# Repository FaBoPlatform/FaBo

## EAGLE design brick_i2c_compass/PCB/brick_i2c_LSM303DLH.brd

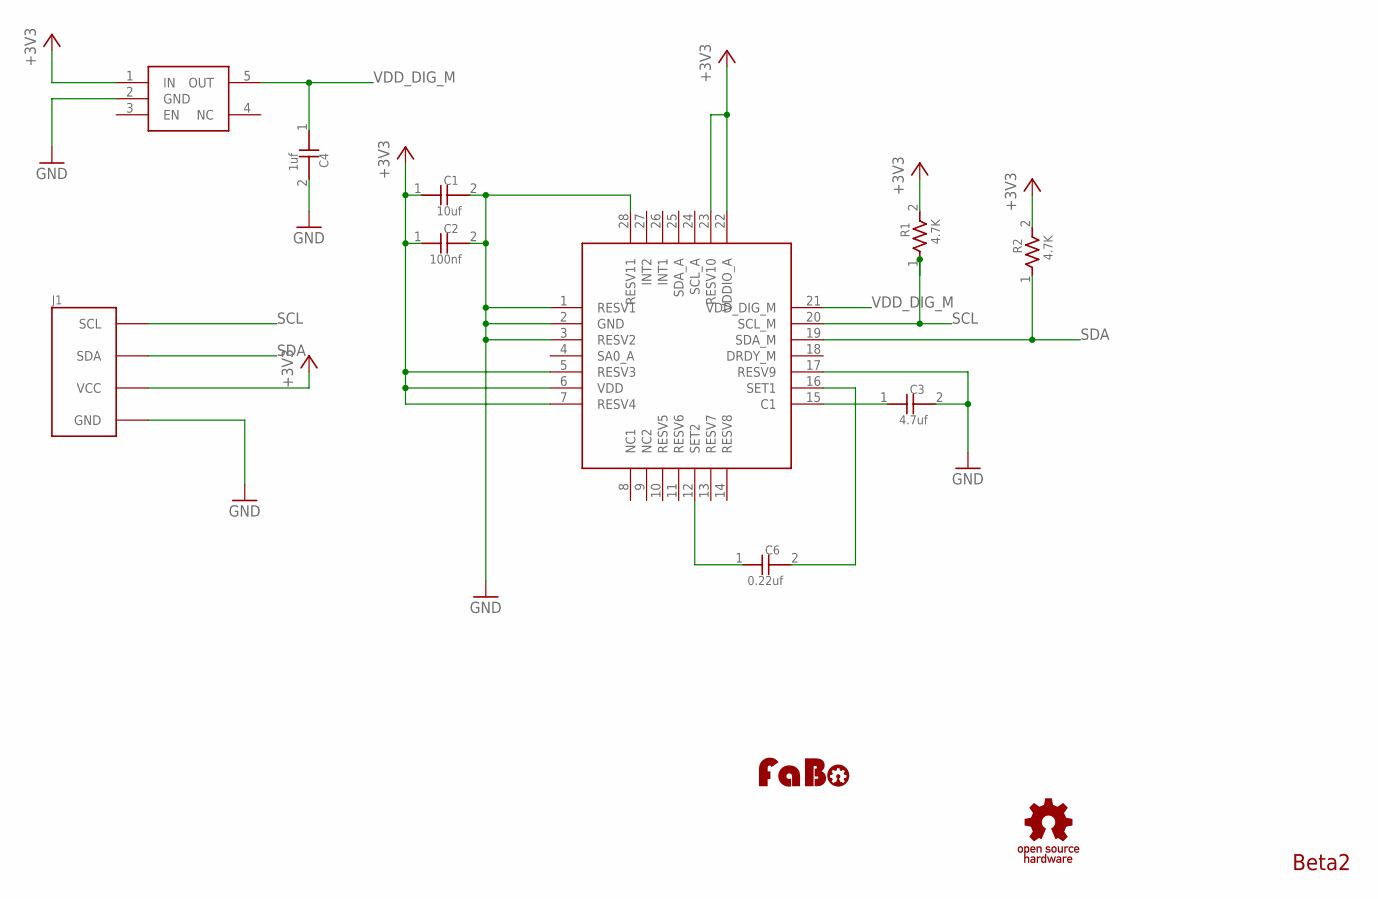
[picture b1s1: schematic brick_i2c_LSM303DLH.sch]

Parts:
C1: 10uf; 0603
C2: 100nf; 0603
C3: 4.7uf; 0603
C4: 1uf; 0603
C6: 0.22uf; 0603
J1: BRICK_I2C
R1, R2: 4.7K; 0603
U$2: ST-LSM303DLH; LGA-28
U$3: TI-TLV70018DDCT; SOT23-5
U$4: LOGO_OSHW_T-M; LOGO_OSHW_T_M
U$5: LOGO_FABO-M; LOGO_FABO_M

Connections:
+3V3: C1.1, C2.1, J1.VCC, R1.2, R2.2, U$2.5 (RESV3), U$2.6 (VDD), U$2.7 (RESV4), U$2.22 (VDDIO_A), U$2.23 (RESV10), U$3.1 (IN)
GND: C1.2, C2.2, C3.2, C4.2, J1.GND, U$2.1 (RESV1), U$2.2 (GND), U$2.3 (RESV2), U$2.17 (RESV9), U$2.28 (RESV11), U$3.2 (GND)
unnamed: C6.1, U$2.12 (SET2)
unnamed: C6.2, U$2.16 (SET1)
unnamed: C3.1, U$2.15 (C1)
SCL: J1.SCL, R1.1, U$2.20 (SCL_M)
SDA: J1.SDA, R2.1, U$2.19 (SDA_M)
VDD_DIG_M: C4.1, U$2.21 (VDD_DIG_M), U$3.5 (OUT)

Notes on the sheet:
Beta2

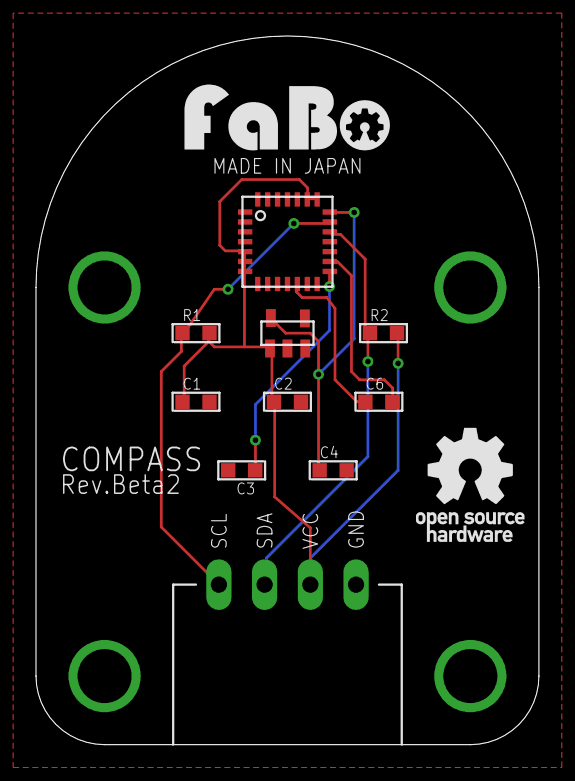
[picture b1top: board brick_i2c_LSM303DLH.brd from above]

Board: 2 copper layers, 27.9 x 39.4 mm, 12 parts (0 on the bottom side), 8 nets.

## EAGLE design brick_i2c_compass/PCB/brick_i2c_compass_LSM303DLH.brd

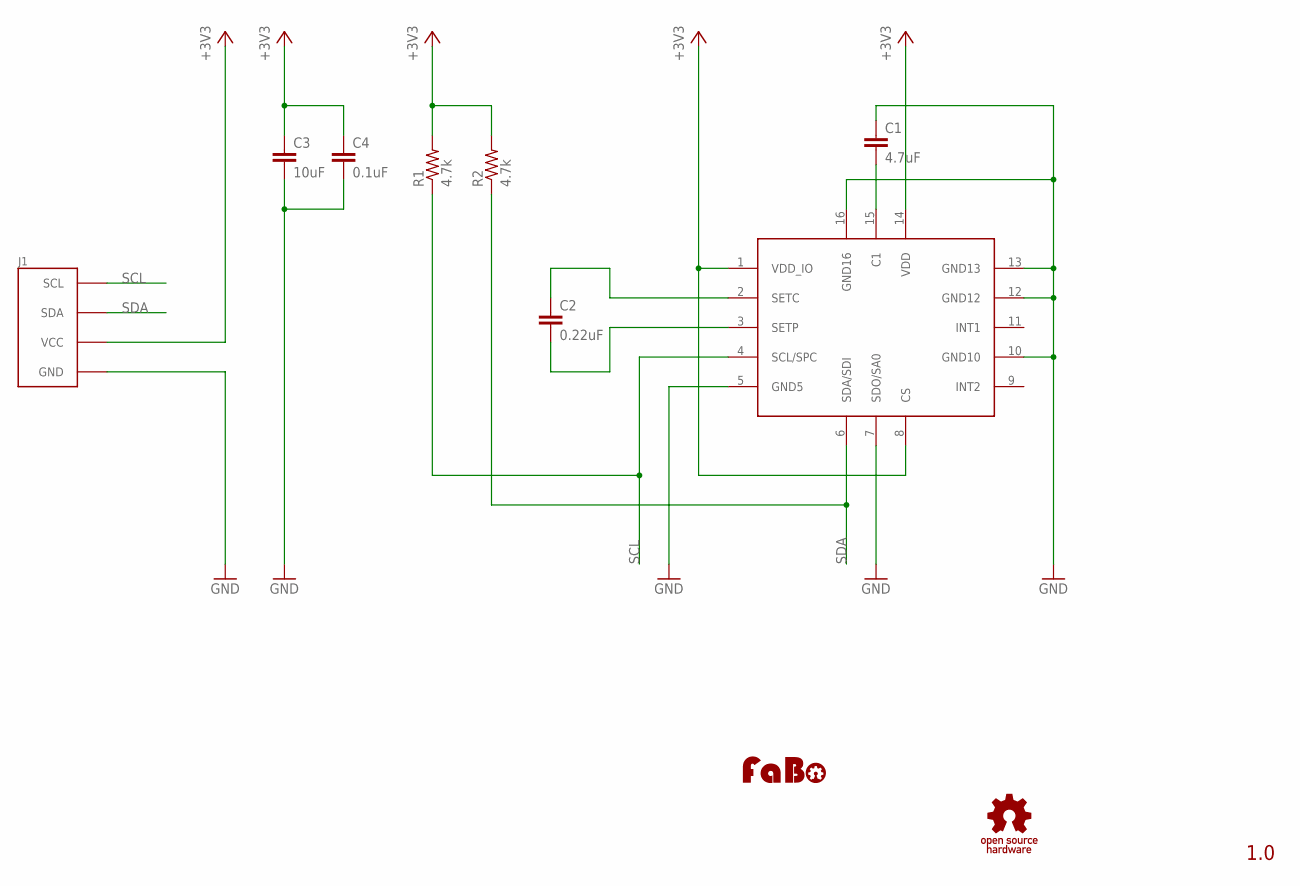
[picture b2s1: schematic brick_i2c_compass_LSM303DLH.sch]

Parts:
C1: 4.7uF; EIA0603
C2: 0.22uF; EIA0603
C3: 10uF; EIA0603
C4: 0.1uF; EIA0603
J1: BRICK_I2C
R1, R2: 4.7k; EIA0603
U$2: ST-LSM303DLH
U$4: LOGO_OSHW_T-M; LOGO_OSHW_T_M
U$5: LOGO_FABO-M; LOGO_FABO_M

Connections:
+3V3: C3.1, C4.1, J1.VCC, R1.2, R2.2, U$2.1 (VDD_IO), U$2.8 (CS), U$2.14 (VDD)
GND: C1.1, C3.2, C4.2, J1.GND, U$2.5 (GND5), U$2.7 (SDO/SA0), U$2.10 (GND10), U$2.12 (GND12), U$2.13 (GND13), U$2.16 (GND16)
unnamed: C2.1, U$2.2 (SETC)
unnamed: C2.2, U$2.3 (SETP)
unnamed: C1.2, U$2.15 (C1)
SCL: J1.SCL, R1.1, U$2.4 (SCL/SPC)
SDA: J1.SDA, R2.1, U$2.6 (SDA/SDI)

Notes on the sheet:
1.0

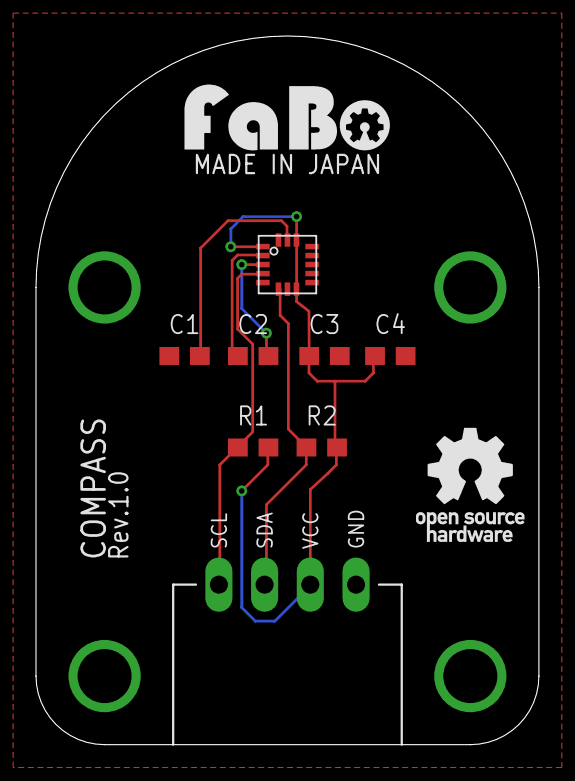
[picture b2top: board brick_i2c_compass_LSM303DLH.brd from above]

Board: 2 copper layers, 27.9 x 39.4 mm, 10 parts (0 on the bottom side), 7 nets.

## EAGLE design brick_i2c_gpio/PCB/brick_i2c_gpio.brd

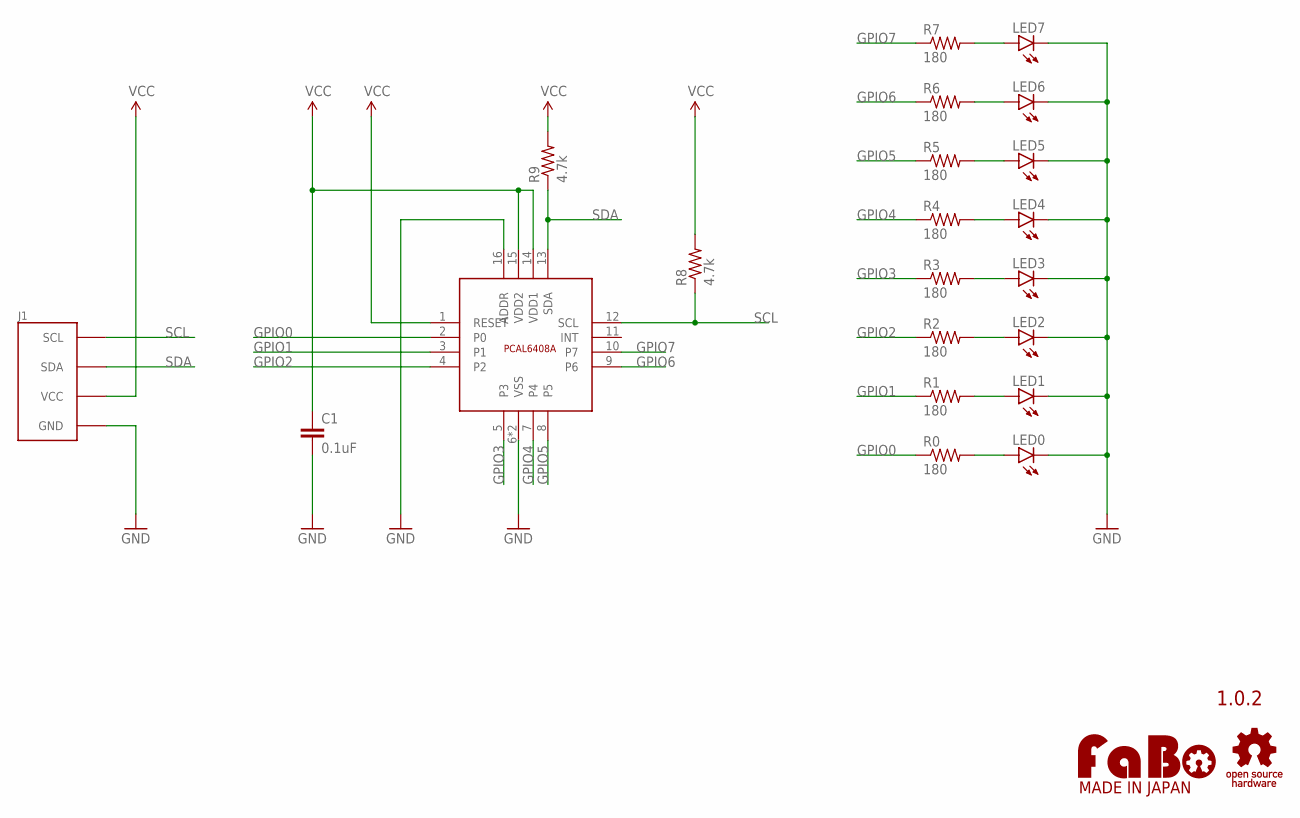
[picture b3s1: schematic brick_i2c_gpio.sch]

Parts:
C1: 0.1uF; EIA0603
J1: BRICK_I2C
LED0, LED1, LED2, LED3, LED4, LED5, LED6, LED7: LED-EIA0603; EIA0603-LED
R0, R1, R2, R3, R4, R5, R6, R7: 180; EIA0603
R8, R9: 4.7k; EIA0603
U$2: LOGO_OSHW-T_M; LOGO_OSHW_T_M
U$4: LOGO_FABO-M; LOGO_FABO_M
U$5: NX-PCAL6408A; NXP-PCAL6408A

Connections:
GND: C1.2, J1.GND, LED0.C, LED1.C, LED2.C, LED3.C, LED4.C, LED5.C, LED6.C, LED7.C, U$5.6 (VSS), U$5.16 (ADDR), U$5.17 (VSS)
GPIO0: R0.1, U$5.2 (P0)
GPIO1: R1.1, U$5.3 (P1)
GPIO2: R2.1, U$5.4 (P2)
GPIO3: R3.1, U$5.5 (P3)
GPIO4: R4.1, U$5.7 (P4)
GPIO5: R5.1, U$5.8 (P5)
GPIO6: R6.1, U$5.9 (P6)
GPIO7: R7.1, U$5.10 (P7)
unnamed: LED7.A, R7.2
unnamed: LED6.A, R6.2
unnamed: LED5.A, R5.2
unnamed: LED4.A, R4.2
unnamed: LED3.A, R3.2
unnamed: LED2.A, R2.2
unnamed: LED1.A, R1.2
unnamed: LED0.A, R0.2
SCL: J1.SCL, R8.1, U$5.12 (SCL)
SDA: J1.SDA, R9.1, U$5.13 (SDA)
VCC: C1.1, J1.VCC, R8.2, R9.2, U$5.1 (RESET), U$5.14 (VDD1), U$5.15 (VDD2)

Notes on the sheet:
1.0.2

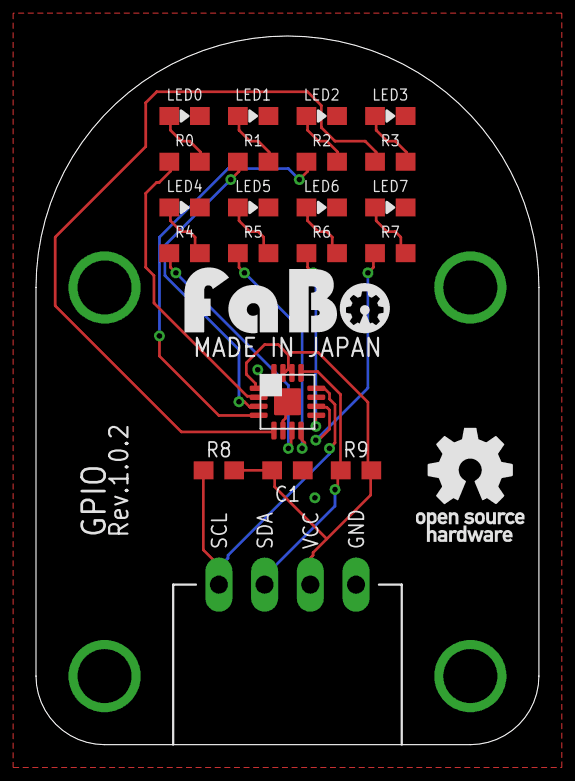
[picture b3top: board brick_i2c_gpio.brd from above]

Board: 2 copper layers, 27.9 x 39.4 mm, 23 parts (0 on the bottom side), 20 nets.

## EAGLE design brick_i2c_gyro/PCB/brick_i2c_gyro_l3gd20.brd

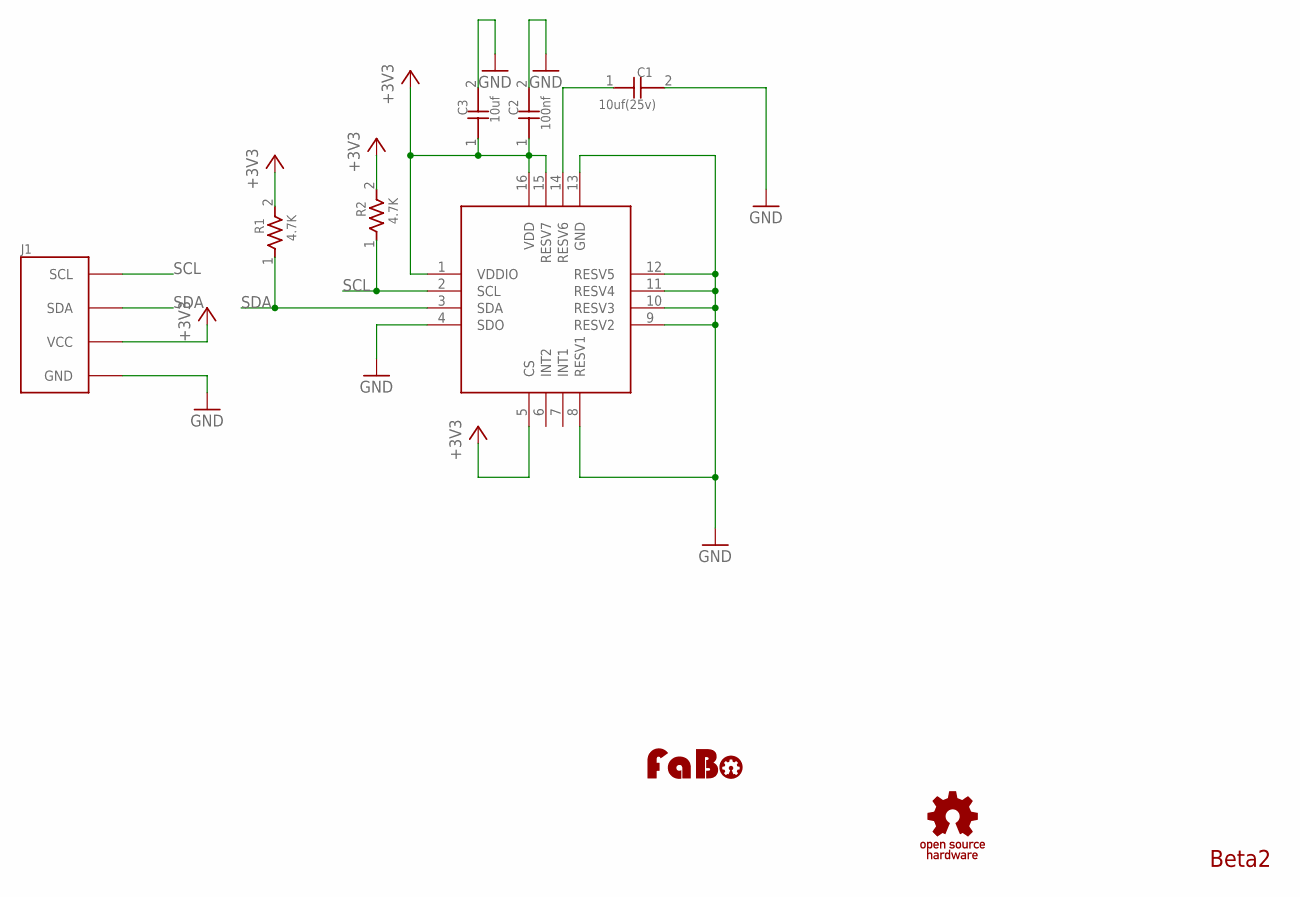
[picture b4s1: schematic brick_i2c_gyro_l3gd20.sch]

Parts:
C1: 10uf(25v); 0603
C2: 100nf; 0603
C3: 10uf; 0603
J1: BRICK_I2C
R1, R2: 4.7K; 0603
U$1: LOGO_OSHW_T-M; LOGO_OSHW_T_M
U$3: ST-L3GD20; LGA-16
U$4: LOGO_FABO-M; LOGO_FABO_M

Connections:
+3V3: C2.1, C3.1, J1.VCC, R1.2, R2.2, U$3.1 (VDDIO), U$3.5 (CS), U$3.15 (RESV7), U$3.16 (VDD)
GND: C1.2, C2.2, C3.2, J1.GND, U$3.4 (SDO), U$3.8 (RESV1), U$3.9 (RESV2), U$3.10 (RESV3), U$3.11 (RESV4), U$3.12 (RESV5), U$3.13 (GND)
unnamed: C1.1, U$3.14 (RESV6)
SCL: J1.SCL, R2.1, U$3.2 (SCL)
SDA: J1.SDA, R1.1, U$3.3 (SDA)

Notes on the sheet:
Beta2

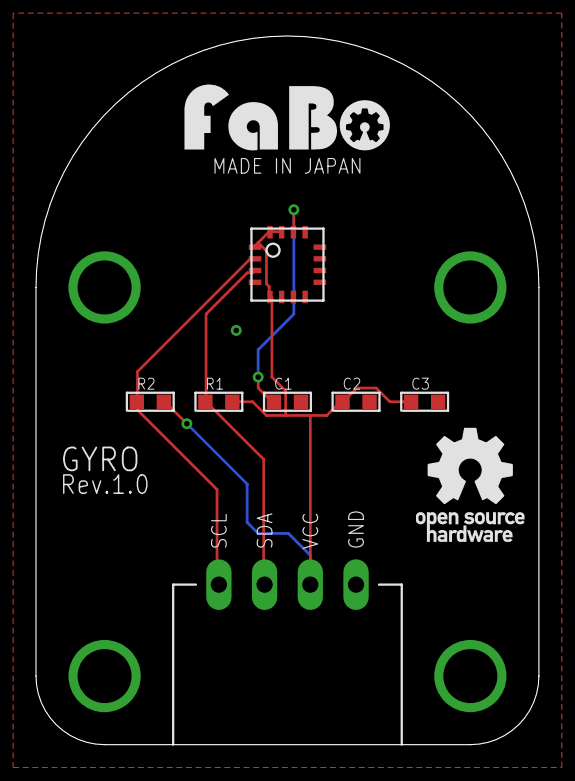
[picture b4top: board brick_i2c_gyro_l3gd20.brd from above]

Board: 2 copper layers, 27.9 x 39.4 mm, 9 parts (0 on the bottom side), 5 nets.

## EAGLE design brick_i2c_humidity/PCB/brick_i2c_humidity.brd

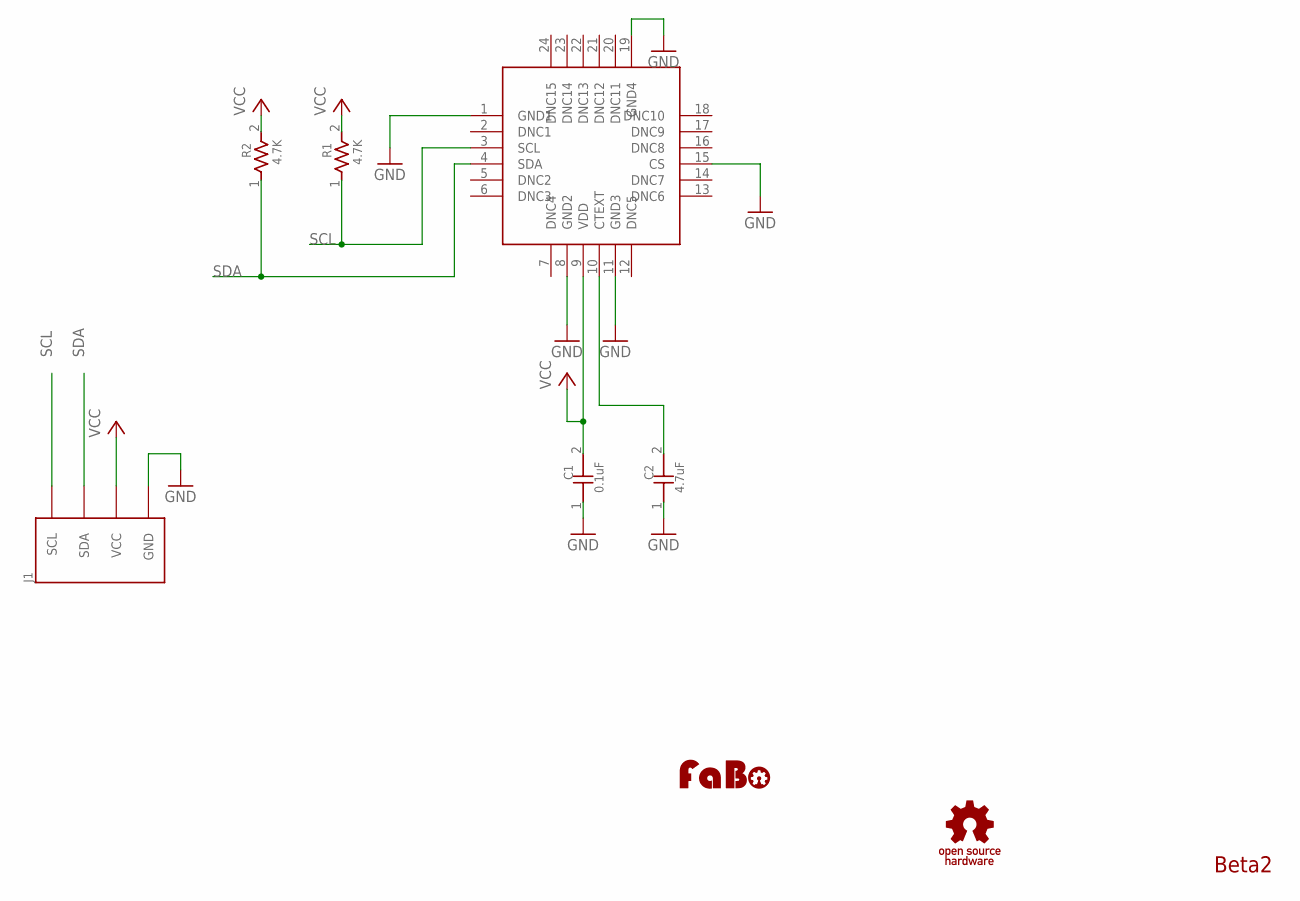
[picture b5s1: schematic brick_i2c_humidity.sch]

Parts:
C1: 0.1uF; 0603
C2: 4.7uF; 0603
J1: BRICK_I2C
R1, R2: 4.7K; 0603
SI1: SILICONLAB-SI7005
U$2: LOGO_FABO-M; LOGO_FABO_M
U$4: LOGO_OSHW_T-M; LOGO_OSHW_T_M

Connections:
GND: C1.1, C2.1, J1.GND, SI1.1 (GND1), SI1.8 (GND2), SI1.11 (GND3), SI1.15 (CS), SI1.19 (GND4)
unnamed: C2.2, SI1.10 (CTEXT)
SCL: J1.SCL, R1.1, SI1.3 (SCL)
SDA: J1.SDA, R2.1, SI1.4 (SDA)
VCC: C1.2, J1.VCC, R1.2, R2.2, SI1.9 (VDD)

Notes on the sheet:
Beta2

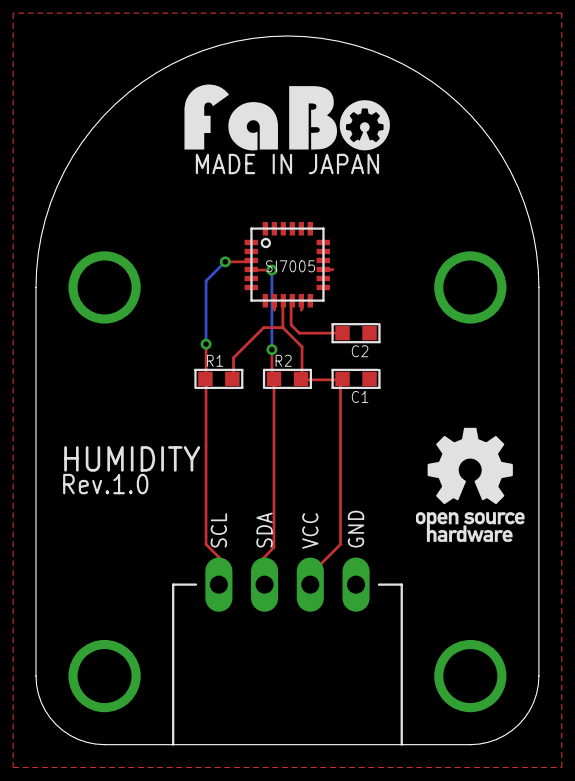
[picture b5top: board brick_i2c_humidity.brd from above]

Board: 2 copper layers, 27.9 x 39.4 mm, 8 parts (0 on the bottom side), 5 nets.

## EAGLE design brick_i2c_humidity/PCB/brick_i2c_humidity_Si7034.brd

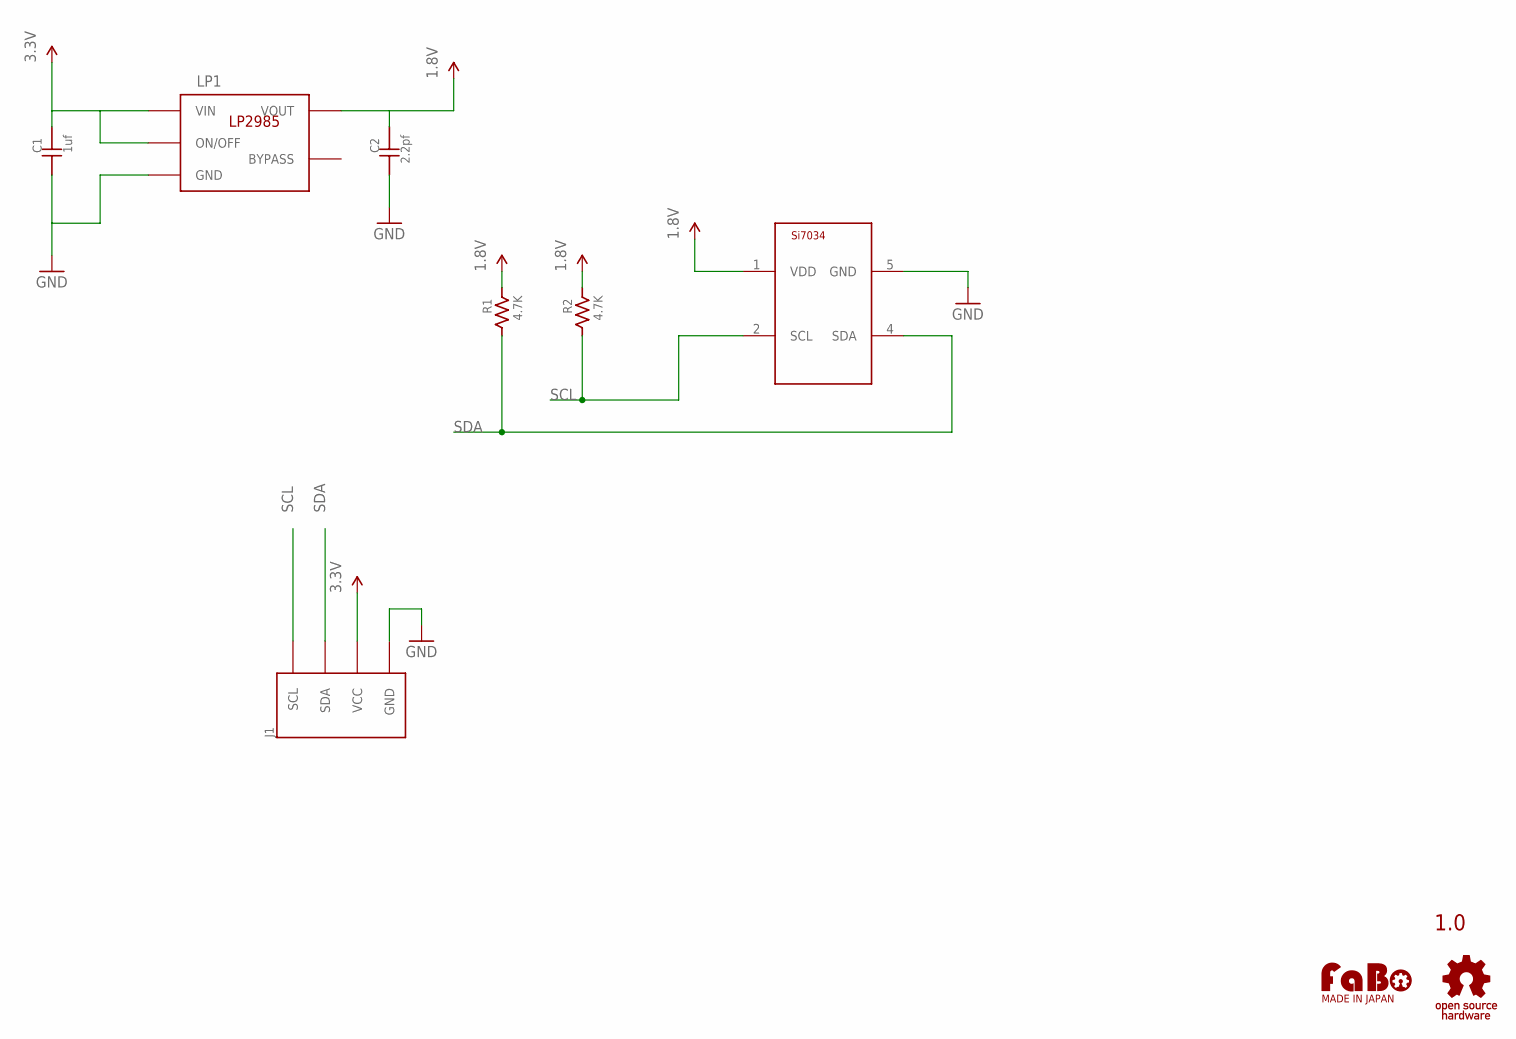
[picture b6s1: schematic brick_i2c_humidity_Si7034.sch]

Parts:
C1: 1uf; 0603
C2: 2.2pf; 0603
J1: BRICK_I2C
LP1: TI-LP2985-18DBVT; TI-LP2985
R1, R2: 4.7K; 0603
U$2: LOGO_FABO-M; LOGO_FABO_M
U$3: SILICONLABS-SI7034
U$4: LOGO_OSHW_T-M; LOGO_OSHW_T_M

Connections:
1.8V: C2.2, LP1.5 (VOUT), R1.2, R2.2, U$3.1 (VDD)
3.3V: C1.2, J1.VCC, LP1.1 (VIN), LP1.3 (ON/OFF)
GND: C1.1, C2.1, J1.GND, LP1.2 (GND), U$3.5 (GND)
SCL: J1.SCL, R2.1, U$3.2 (SCL)
SDA: J1.SDA, R1.1, U$3.4 (SDA)

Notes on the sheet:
1.0

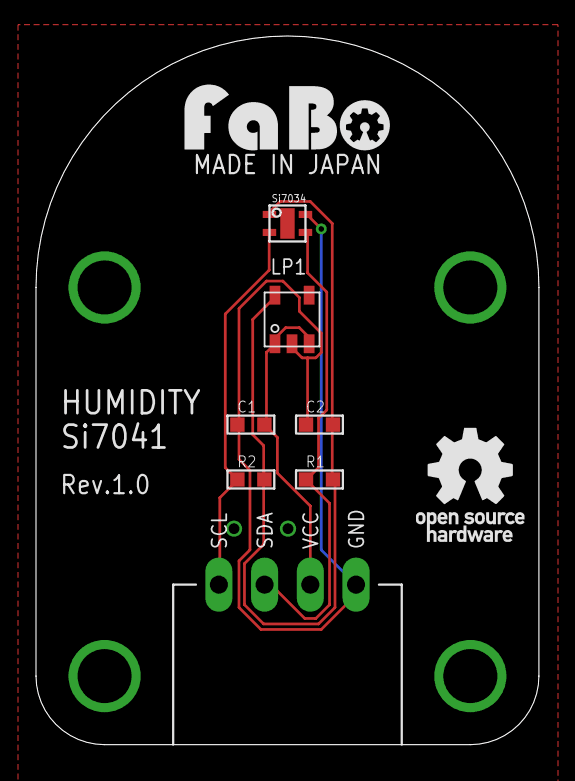
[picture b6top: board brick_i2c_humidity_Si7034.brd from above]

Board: 2 copper layers, 27.9 x 39.4 mm, 9 parts (0 on the bottom side), 5 nets.

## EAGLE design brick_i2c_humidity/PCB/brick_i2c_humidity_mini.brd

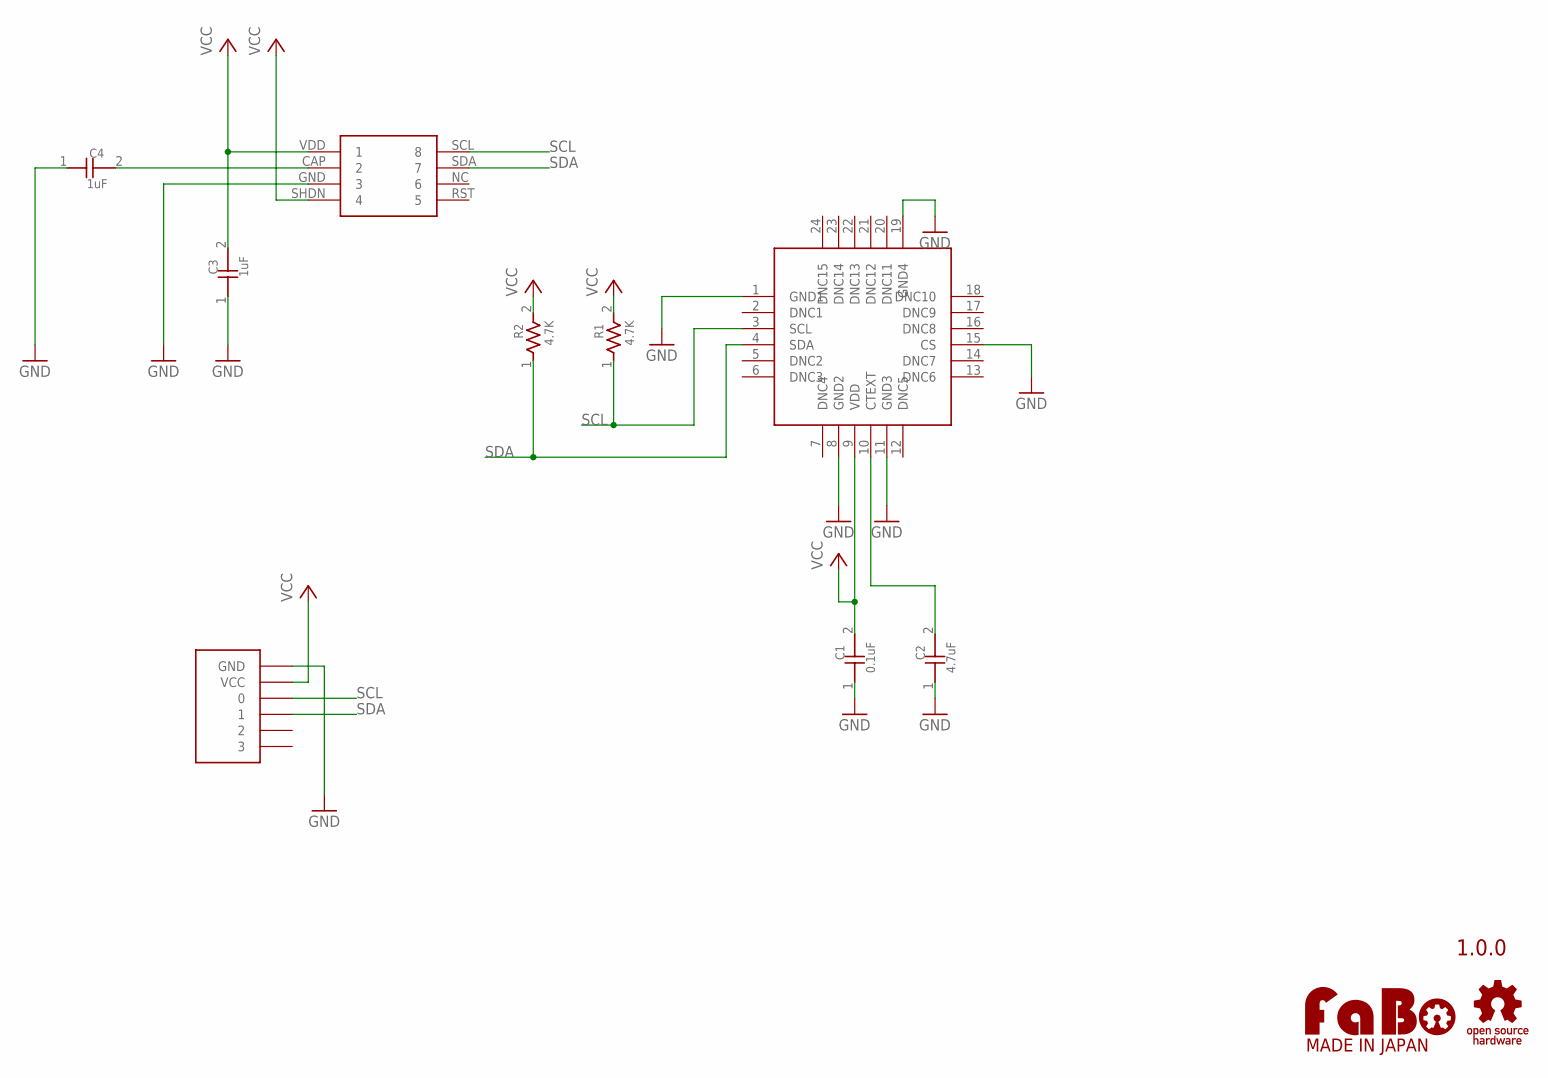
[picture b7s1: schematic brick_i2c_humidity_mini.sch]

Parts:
C1: 0.1uF; 0603
C2: 4.7uF; 0603
C3, C4: 1uF; 0603
R1, R2: 4.7K; 0603
SI1: SILICONLAB-SI7005
U$2: LOGO_OSHW-S_BOTTOM; LOGO_OSHW_S_BOTTOM
U$3: I2C-MPL115A2; I2C-MLP115A2
U$4: LOGO_FABO-S_BOTTOM; LOGO_FABO_S_BOTTOM
U$5: FABO-NANO

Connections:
GND: C1.1, C2.1, C3.1, C4.1, SI1.1 (GND1), SI1.8 (GND2), SI1.11 (GND3), SI1.15 (CS), SI1.19 (GND4), U$3.GND (3), U$5.GND
unnamed: C2.2, SI1.10 (CTEXT)
unnamed: C4.2, U$3.CAP (2)
SCL: R1.1, SI1.3 (SCL), U$3.SCL (8), U$5.0
SDA: R2.1, SI1.4 (SDA), U$3.SDA (7), U$5.1
VCC: C1.2, C3.2, R1.2, R2.2, SI1.9 (VDD), U$3.SHDN (4), U$3.VDD (1), U$5.VCC

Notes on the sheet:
1.0.0

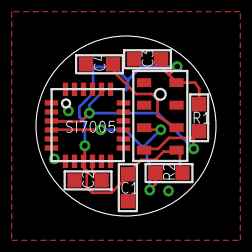
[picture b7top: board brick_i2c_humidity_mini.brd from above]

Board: 2 copper layers, 10.0 x 10.0 mm, 11 parts (0 on the bottom side), 6 nets.

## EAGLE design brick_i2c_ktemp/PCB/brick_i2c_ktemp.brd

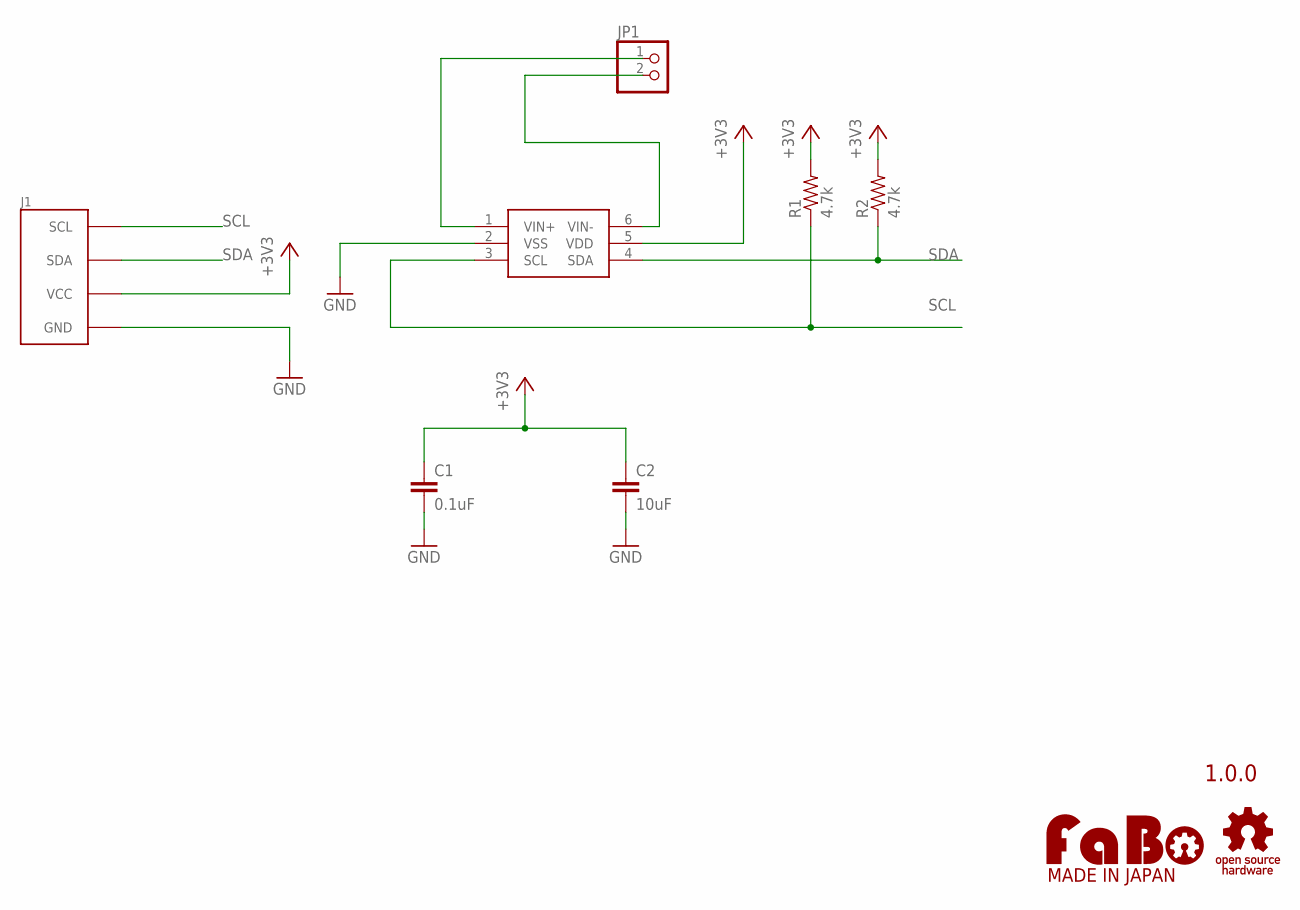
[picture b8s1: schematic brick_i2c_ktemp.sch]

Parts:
C1: 0.1uF; EIA0603
C2: 10uF; EIA0603
J1: BRICK_I2C
JP1: PINHD-1X2; 1X02
R1, R2: 4.7k; EIA0603
U$2: MICROCHIP-MCP3421
U$3: LOGO_OSHW_T-M; LOGO_OSHW_T_M
U$4: LOGO_FABO-M; LOGO_FABO_M

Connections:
+3V3: C1.1, C2.1, J1.VCC, R1.2, R2.2, U$2.5 (VDD)
GND: C1.2, C2.2, J1.GND, U$2.2 (VSS)
unnamed: JP1.2, U$2.6 (VIN-)
unnamed: JP1.1, U$2.1 (VIN+)
SCL: J1.SCL, R1.1, U$2.3 (SCL)
SDA: J1.SDA, R2.1, U$2.4 (SDA)

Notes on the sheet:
1.0.0

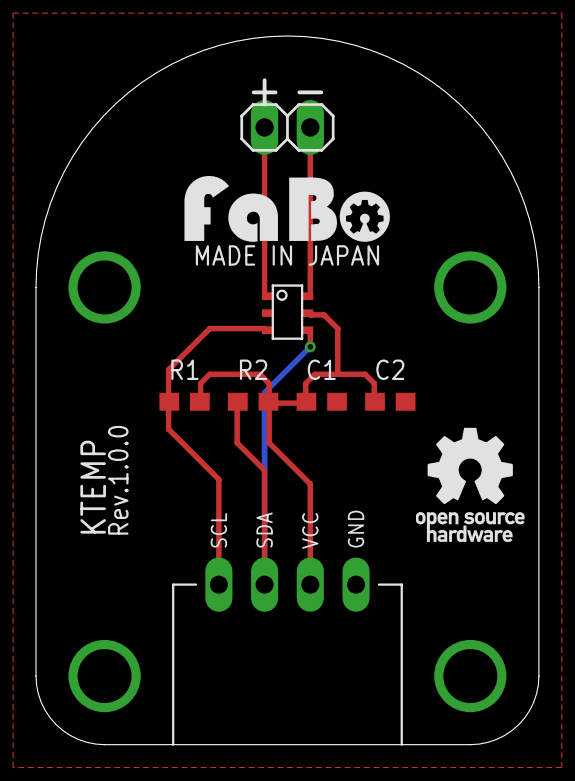
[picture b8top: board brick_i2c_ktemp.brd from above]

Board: 2 copper layers, 27.9 x 39.4 mm, 9 parts (0 on the bottom side), 6 nets.

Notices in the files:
parts and their libraries:
FaBo-etc: Released under the Creative Commons Attribution-ShareAlike 4.0 License
https://creativecommons.org/licenses/by-sa/4.0
FaBo-etc: Released under the Creative Commons
